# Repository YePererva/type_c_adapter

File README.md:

# [WIP] USB Type C Receptacle to USB 2.0 breakout board

A few breakout boards for USB Type C Receptacle to breadboard and flex ribbon cables.

## Purpose

Fix / upgrade some equipment that is still using previous generation of USB connectors

## Why?

1. Because most of found adapter boards are missing (or have only 1) pull-down 5K1 resistors, while 2 of those are required
2. I also want to have alternative option with EDS protection IC
3. I wanted to have extra opportunity to use 5-pin flat ribbon cable instead of loose wires

Additionally:

- use the size of SMD components that are still solderable manually (0805 Resistors)

## Details

This repository contains 2 kinds of breakout board:

- simple
- with ESD protection: utilizing USBLC6-2SC6 IC (same as used on STM32-Nucleo boards)

Both versions contain:
- 16-pin USB Type Receptacle
- 4-pin regular breadboard-friendly pin-header
- 2 x 5-pin soldering footprints for flat-ribbon cable with the same pitch as USB Micro connector
	- straight pin-out
	- mirrored pin-out

Solder to the footprint depending on the side, you'll install this adapter in your device. Silkscreen provides details regrading the pin-out.

## Visuals

| Variation | Top-view | Bottom view |
| :---         |     :---:      | :---: |
| Simple   |      |     |
| With ESD     |       |       |

## Remarks

There are a few tended vias used in these PCB, which is not ussually recomended. However, it seem to be the safest way of having some connections under the USB connector.  

## Thoughts on further

The only two things I would like to improove in these PCB are:

- to find pin-to-pin compatible USB Type C connector with water-proof housing
- having extra the PCB mounting bracket (like the availble with M2 screws) 
- modify the pin-headers to castelated holes

## Inspirations

There are a few similar solutions on market. Not all of them has even footprints for pull-down resistors, and none of them have footprints for flex flat cable.

### Regular breakout boards

Available from manufacturers as [Adafruit](https://www.adafruit.com/product/4090), [Sparkfun](https://www.sparkfun.com/sparkfun-usb-c-breakout.html), [Popolu](https://www.pololu.com/product/2585), etc.

Usually have access to all additional pins (`CC1`, `CC2`, etc.) which make them large. However these variations are breadboard friendly.

|    |    |
| -- | -- |

### Simpistic breakout boards

Available from [Adafruit](https://www.adafruit.com/product/5180) and and some not so known brands. Usually very compact and might have the soldering place for breadboard pins.

|    |    |
| -- | -- |

### Other

[μC USB Type C Breakout Board](https://www.tindie.com/products/casualcoders/c-usb-type-c-breakout-board-5-pack/) by [Casual Coders](https://www.tindie.com/stores/casualcoders/) on Tindie.

Also, available on [GitHub](https://github.com/CasualCodersProjects/uC-Breakout)

It seem to be nice, but I don't need access to all 8 pins, it uses small size resistors and can't be used with breadboard.

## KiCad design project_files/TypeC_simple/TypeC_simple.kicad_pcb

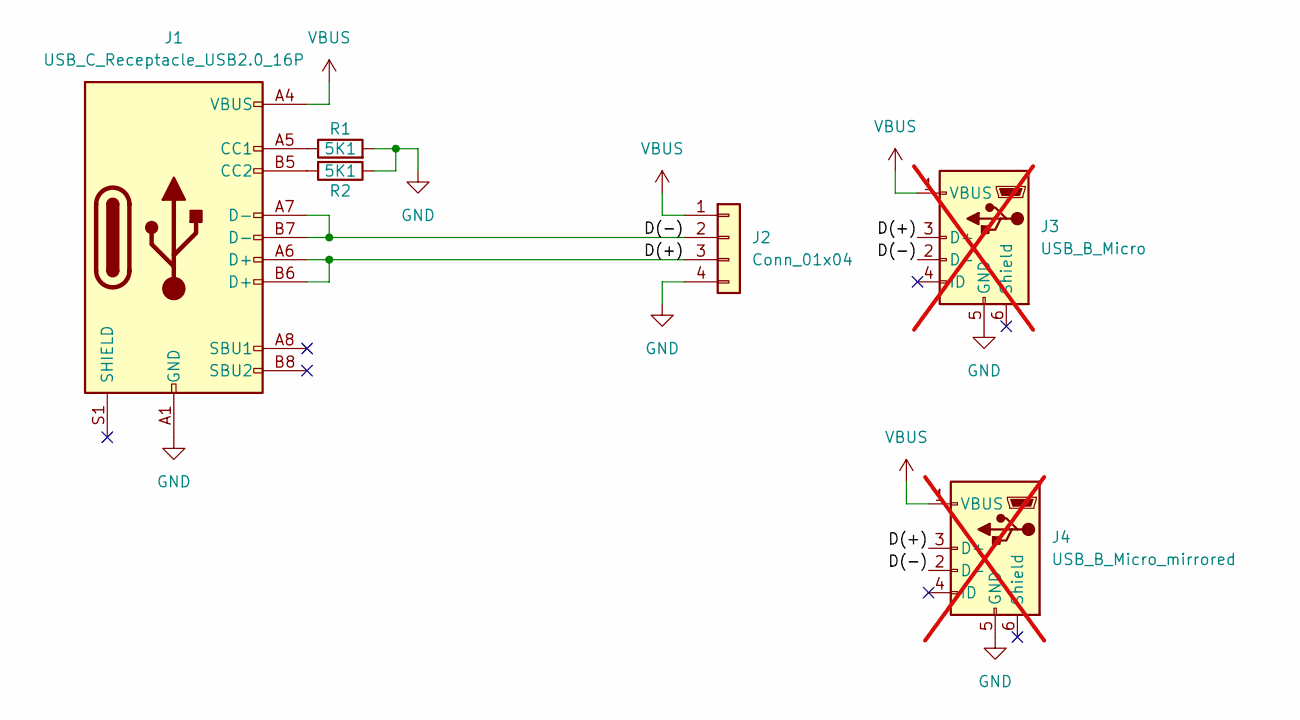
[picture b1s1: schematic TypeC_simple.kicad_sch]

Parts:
J1: USB_C_Receptacle_USB2.0_16P; USB_C_Receptacle_GCT_USB4105-xx-A_16P_TopMnt_Horizontal
J2: Conn_01x04; PinHeader_1x04_P2.54mm_Vertical
J3: USB_B_Micro; USB_Micro-B_Technik_TWP-4002D-H3; not fitted
J4: USB_B_Micro_mirrored; USB_Micro-B_Technik_TWP-4002D-H3; not fitted
R1, R2: 5K1; R_0805_2012Metric

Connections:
/D(+): J1.A6 (D+), J1.B6 (D+), J2.3, J3.3 (D+), J4.3 (D+)
/D(-): J1.A7 (D-), J1.B7 (D-), J2.2, J3.2 (D-), J4.2 (D-)
GND: J1.A1 (GND), J1.A12 (GND), J1.B1 (GND), J1.B12 (GND), J2.4, J3.5 (GND), J4.5 (GND), R1.2, R2.1
unnamed: J1.A5 (CC1), R1.1
unnamed: J1.B5 (CC2), R2.2
VBUS: J1.A4 (VBUS), J1.A9 (VBUS), J1.B4 (VBUS), J1.B9 (VBUS), J2.1, J3.1 (VBUS), J4.1 (VBUS)

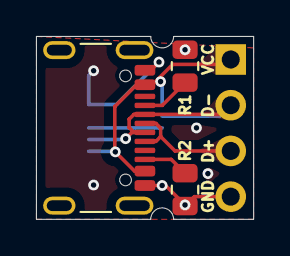
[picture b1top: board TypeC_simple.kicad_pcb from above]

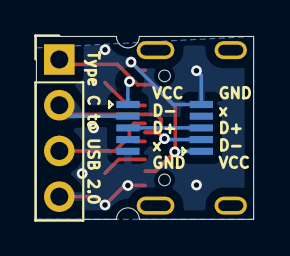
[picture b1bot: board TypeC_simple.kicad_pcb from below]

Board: 2 copper layers, 12.1 x 10.2 mm, 6 parts (3 on the bottom side), 6 nets.

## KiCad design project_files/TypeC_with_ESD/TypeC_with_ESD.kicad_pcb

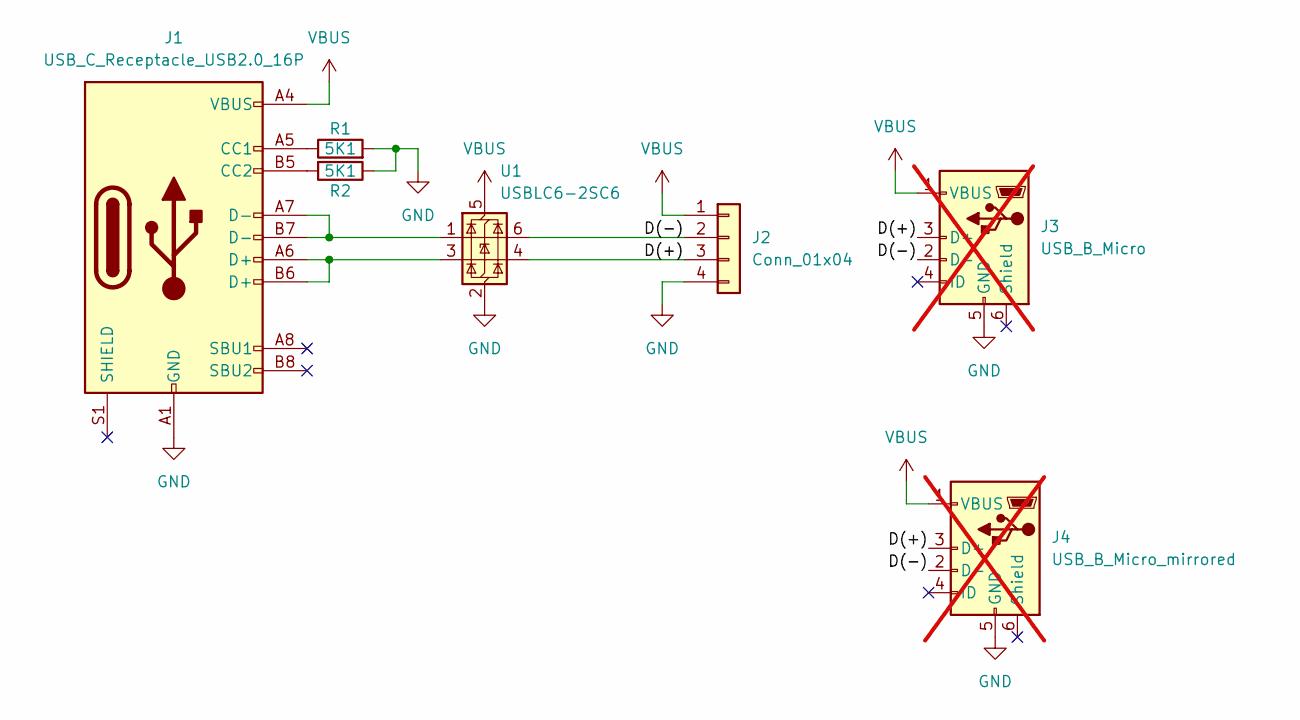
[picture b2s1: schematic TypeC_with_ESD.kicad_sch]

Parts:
J1: USB_C_Receptacle_USB2.0_16P; USB_C_Receptacle_GCT_USB4105-xx-A_16P_TopMnt_Horizontal
J2: Conn_01x04; PinHeader_1x04_P2.54mm_Vertical
J3: USB_B_Micro; USB_Micro-B_Technik_TWP-4002D-H3; not fitted
J4: USB_B_Micro_mirrored; USB_Micro-B_Technik_TWP-4002D-H3; not fitted
R1, R2: 5K1; R_0805_2012Metric
U1: USBLC6-2SC6; SOT-23-6

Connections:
/D(+): J2.3, J3.3 (D+), J4.3 (D+), U1.4 (I/O2)
/D(-): J2.2, J3.2 (D-), J4.2 (D-), U1.6 (I/O1)
GND: J1.A1 (GND), J1.A12 (GND), J1.B1 (GND), J1.B12 (GND), J2.4, J3.5 (GND), J4.5 (GND), R1.2, R2.1, U1.2 (GND)
unnamed: J1.A5 (CC1), R1.1
unnamed: J1.B5 (CC2), R2.2
unnamed: J1.A6 (D+), J1.B6 (D+), U1.3 (I/O2)
unnamed: J1.A7 (D-), J1.B7 (D-), U1.1 (I/O1)
VBUS: J1.A4 (VBUS), J1.A9 (VBUS), J1.B4 (VBUS), J1.B9 (VBUS), J2.1, J3.1 (VBUS), J4.1 (VBUS), U1.5 (VBUS)

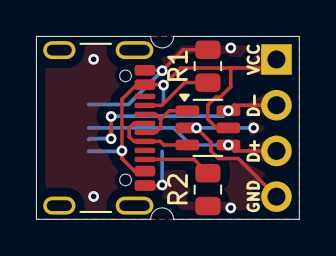
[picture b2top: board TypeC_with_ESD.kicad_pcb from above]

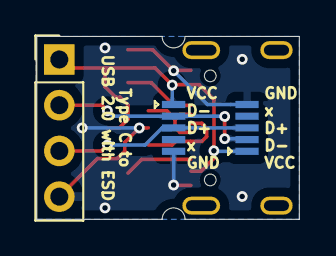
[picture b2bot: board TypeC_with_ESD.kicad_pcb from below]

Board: 2 copper layers, 14.6 x 10.2 mm, 7 parts (3 on the bottom side), 8 nets.

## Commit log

2025-04-06 uploading the project
2025-04-06 Added renders
2025-04-06 Fixing table
2025-04-07 added some visuals
